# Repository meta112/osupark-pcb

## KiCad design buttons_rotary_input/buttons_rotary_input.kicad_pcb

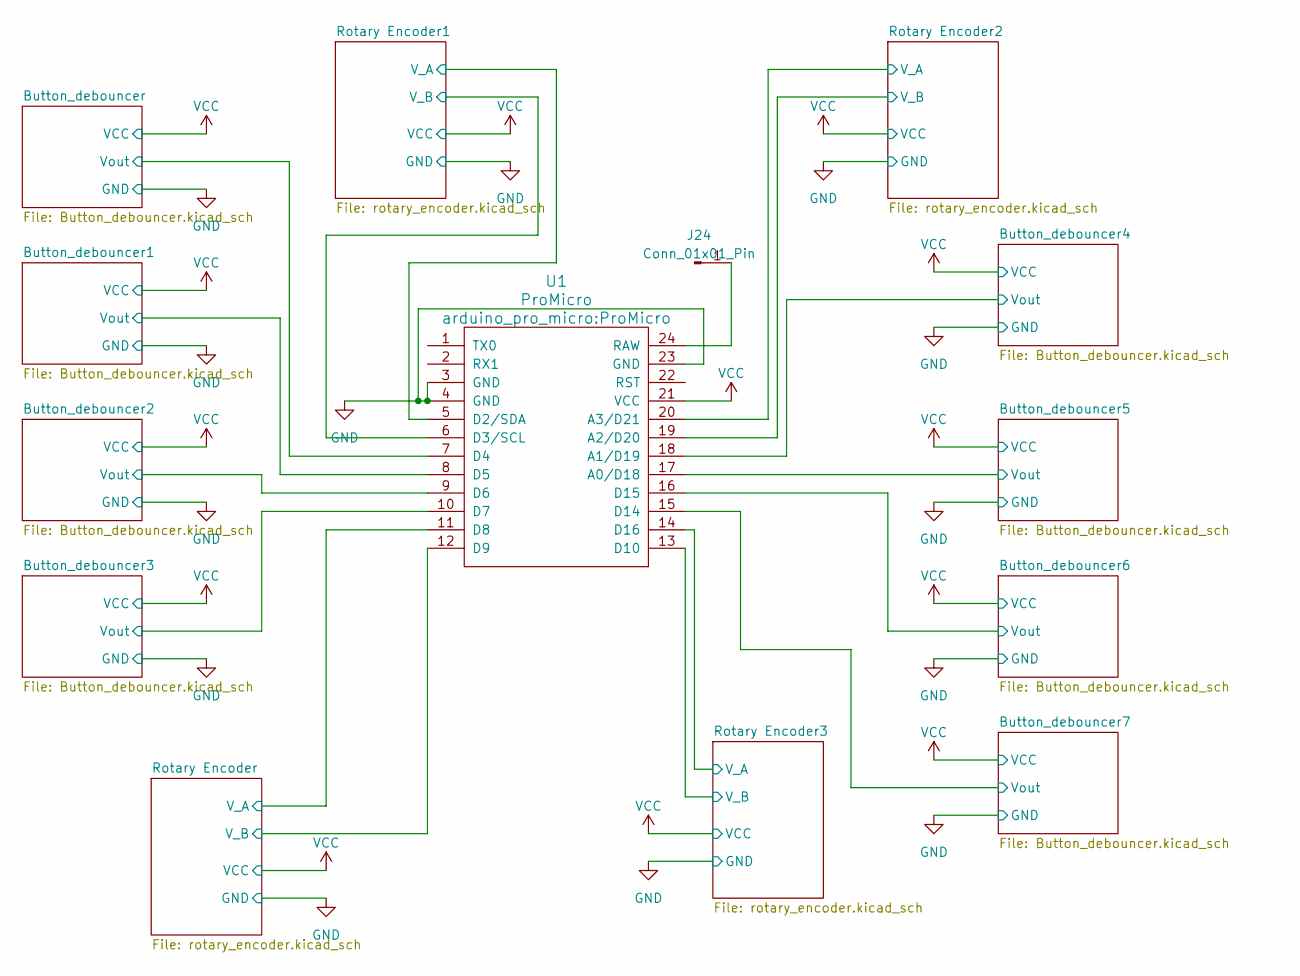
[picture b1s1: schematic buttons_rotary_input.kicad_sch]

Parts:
J24: Conn_01x01_Pin; PinHeader_1x01_P2.54mm_Vertical
U1: ProMicro

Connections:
/Button_debouncer1/Vout: U1.8 (D5); also elsewhere on the board
/Button_debouncer2/Vout: U1.9 (D6); also elsewhere on the board
/Button_debouncer3/Vout: U1.10 (D7); also elsewhere on the board
/Button_debouncer4/Vout: U1.18 (A1/D19); also elsewhere on the board
/Button_debouncer6/Vout: U1.16 (D15); also elsewhere on the board
/Button_debouncer7/Vout: U1.15 (D14); also elsewhere on the board
/Rotary Encoder1/V_A: U1.5 (D2/SDA); also elsewhere on the board
/Rotary Encoder1/V_B: U1.6 (D3/SCL); also elsewhere on the board
/Rotary Encoder2/V_A: U1.20 (A3/D21); also elsewhere on the board
/Rotary Encoder2/V_B: U1.19 (A2/D20); also elsewhere on the board
/Rotary Encoder3/V_A: U1.14 (D16); also elsewhere on the board
/Rotary Encoder3/V_B: U1.13 (D10); also elsewhere on the board
/Rotary Encoder/V_A: U1.11 (D8); also elsewhere on the board
/Rotary Encoder/V_B: U1.12 (D9); also elsewhere on the board
GND: U1.3 (GND), U1.4 (GND), U1.23 (GND); also elsewhere on the board
unnamed: J24.1, U1.24 (RAW)
VCC: U1.21 (VCC); also elsewhere on the board

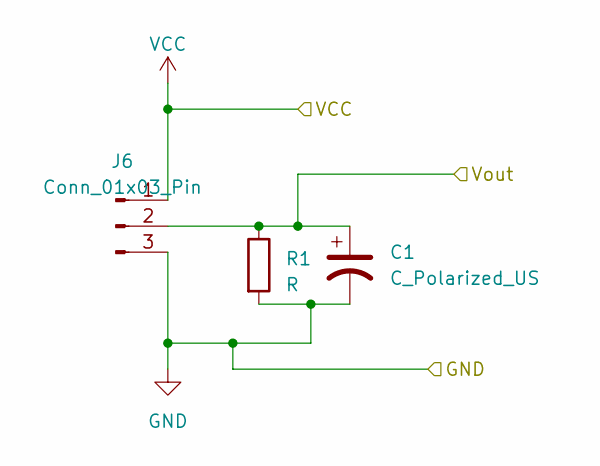
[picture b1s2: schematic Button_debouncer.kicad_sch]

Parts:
C1: C_Polarized_US; CP_Radial_D6.3mm_P2.50mm
J6: Conn_01x03_Pin; PinHeader_1x03_P2.54mm_Vertical
R1: R; R_Axial_DIN0414_L11.9mm_D4.5mm_P15.24mm_Horizontal

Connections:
GND: C1.2, J6.3, R1.2; also elsewhere on the board
VCC: J6.1; also elsewhere on the board

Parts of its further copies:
C2, C3, C4, C5, C6, C7, C8: C_Polarized_US; CP_Radial_D6.3mm_P2.50mm
J1, J2, J3, J4, J5, J7, J8: Conn_01x03_Pin; PinHeader_1x03_P2.54mm_Vertical
R2, R3, R4, R5, R6, R7, R8: R; R_Axial_DIN0414_L11.9mm_D4.5mm_P15.24mm_Horizontal

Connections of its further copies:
/Button_debouncer1/Vout: C2.1, J2.2, R2.1; also elsewhere on the board
/Button_debouncer2/Vout: C3.1, J3.2, R3.1; also elsewhere on the board
/Button_debouncer3/Vout: C4.1, J4.2, R4.1; also elsewhere on the board
/Button_debouncer4/Vout: C5.1, J5.2, R5.1; also elsewhere on the board
/Button_debouncer6/Vout: C7.1, J7.2, R7.1; also elsewhere on the board
/Button_debouncer7/Vout: C8.1, J8.2, R8.1; also elsewhere on the board
GND: C2.2, C3.2, C4.2, C5.2, C6.2, C7.2, C8.2, J1.3, J2.3, J3.3, J4.3, J5.3, J7.3, J8.3, R2.2, R3.2, R4.2, R5.2, R6.2, R7.2, R8.2; also elsewhere on the board
VCC: J1.1, J2.1, J3.1, J4.1, J5.1, J7.1, J8.1; also elsewhere on the board

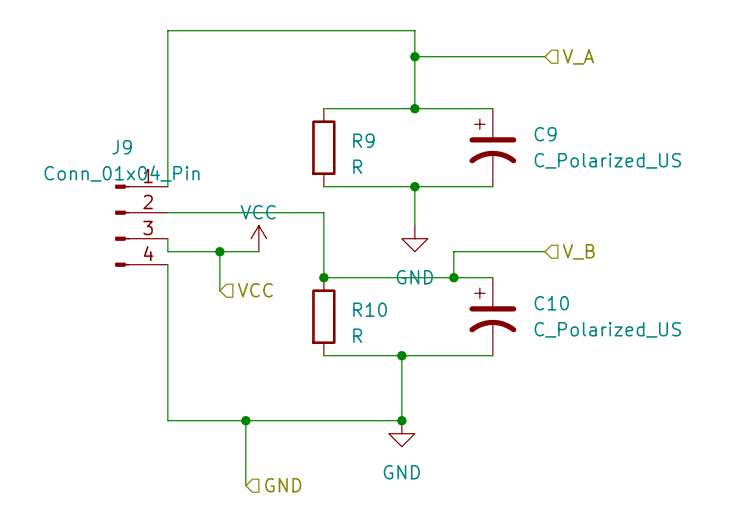
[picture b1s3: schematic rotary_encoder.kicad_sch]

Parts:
C9, C10: C_Polarized_US; CP_Radial_D6.3mm_P2.50mm
J9: Conn_01x04_Pin; PinHeader_1x04_P2.54mm_Vertical
R9, R10: R; R_Axial_DIN0414_L11.9mm_D4.5mm_P15.24mm_Horizontal

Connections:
/Rotary Encoder/V_A: C9.1, J9.1, R9.1; also elsewhere on the board
/Rotary Encoder/V_B: C10.1, J9.2, R10.1; also elsewhere on the board
GND: C9.2, C10.2, J9.4, R9.2, R10.2; also elsewhere on the board
VCC: J9.3; also elsewhere on the board

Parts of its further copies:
C11, C12, C13, C14, C15, C16: C_Polarized_US; CP_Radial_D6.3mm_P2.50mm
J11, J13, J15: Conn_01x04_Pin; PinHeader_1x04_P2.54mm_Vertical
R11, R12, R13, R14, R15, R16: R; R_Axial_DIN0414_L11.9mm_D4.5mm_P15.24mm_Horizontal

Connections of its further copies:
/Rotary Encoder1/V_A: C11.1, J11.1, R11.1; also elsewhere on the board
/Rotary Encoder1/V_B: C12.1, J11.2, R12.1; also elsewhere on the board
/Rotary Encoder2/V_A: C13.1, J13.1, R13.1; also elsewhere on the board
/Rotary Encoder2/V_B: C14.1, J13.2, R14.1; also elsewhere on the board
/Rotary Encoder3/V_A: C15.1, J15.1, R15.1; also elsewhere on the board
/Rotary Encoder3/V_B: C16.1, J15.2, R16.1; also elsewhere on the board
GND: C11.2, C12.2, C13.2, C14.2, C15.2, C16.2, J11.4, J13.4, J15.4, R11.2, R12.2, R13.2, R14.2, R15.2, R16.2; also elsewhere on the board
VCC: J11.3, J13.3, J15.3; also elsewhere on the board

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
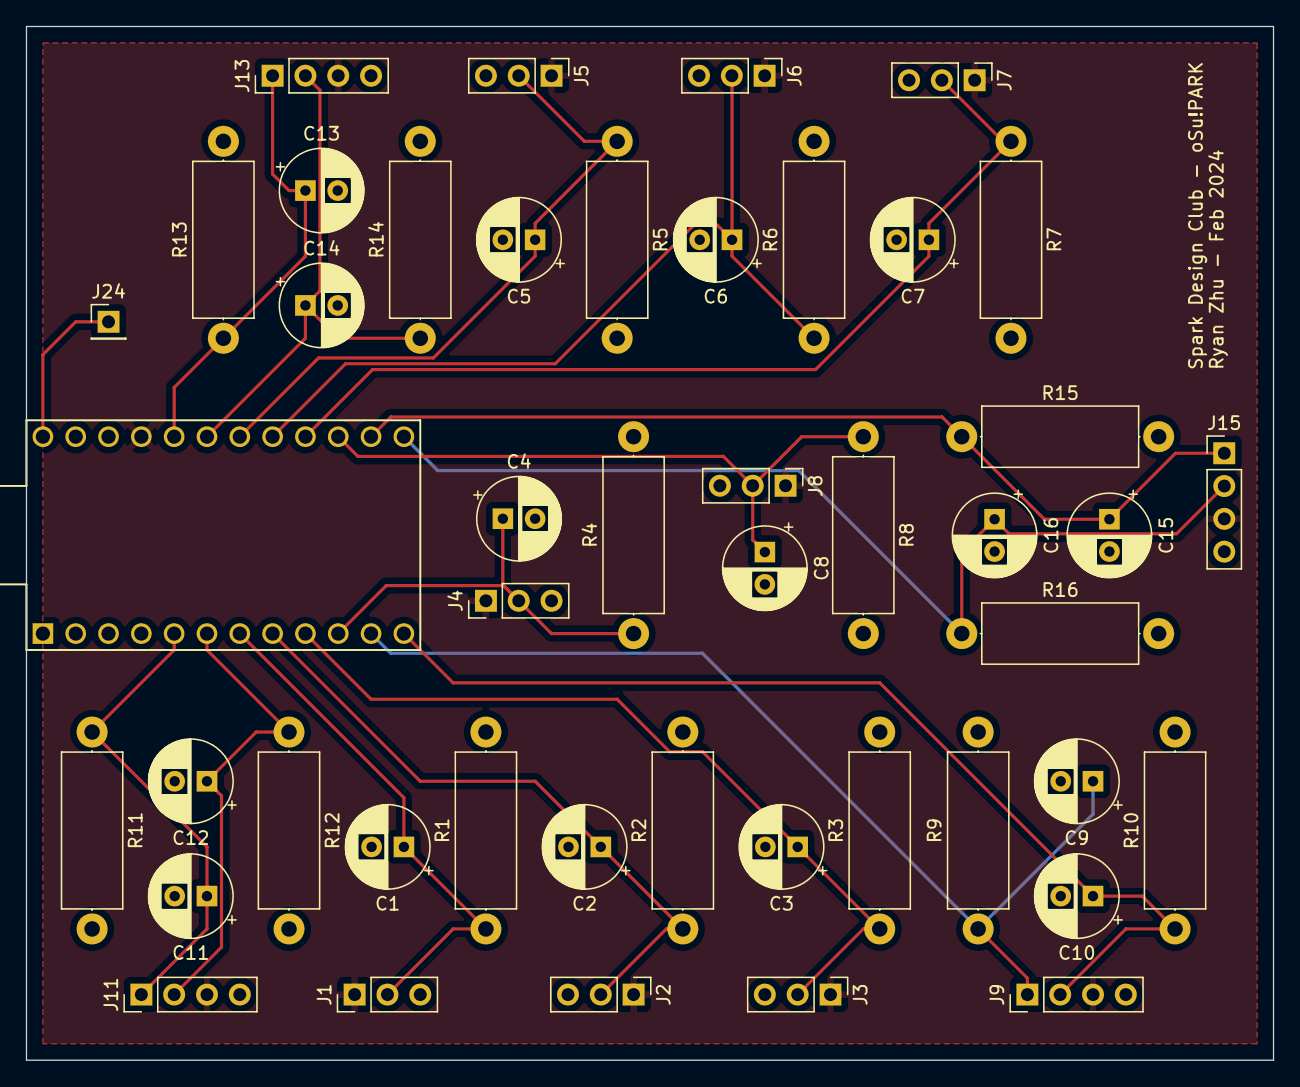
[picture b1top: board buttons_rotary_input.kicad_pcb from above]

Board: 2 copper layers, 96.5 x 80.0 mm, 46 parts (0 on the bottom side), 19 nets.

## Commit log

2024-02-04 Upload pcb for button + rotary encoder debounce
